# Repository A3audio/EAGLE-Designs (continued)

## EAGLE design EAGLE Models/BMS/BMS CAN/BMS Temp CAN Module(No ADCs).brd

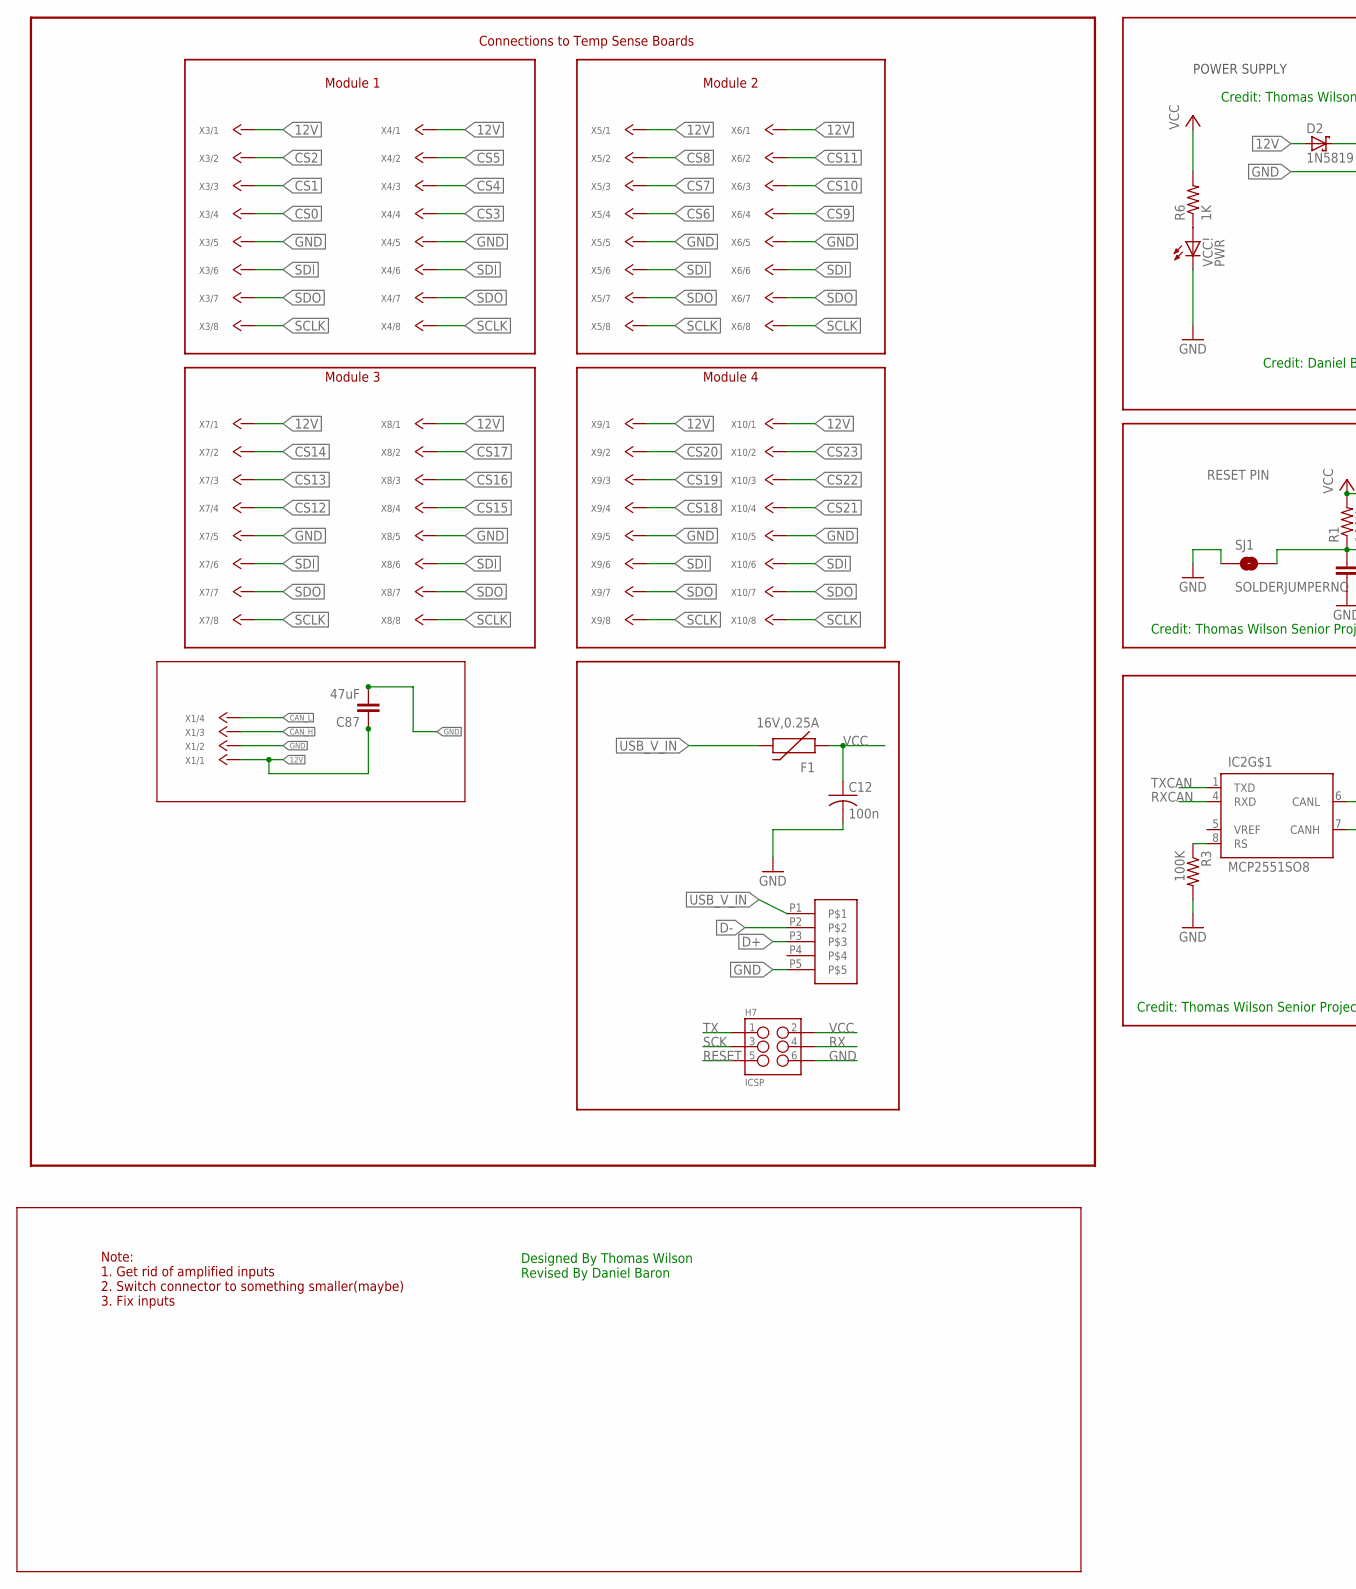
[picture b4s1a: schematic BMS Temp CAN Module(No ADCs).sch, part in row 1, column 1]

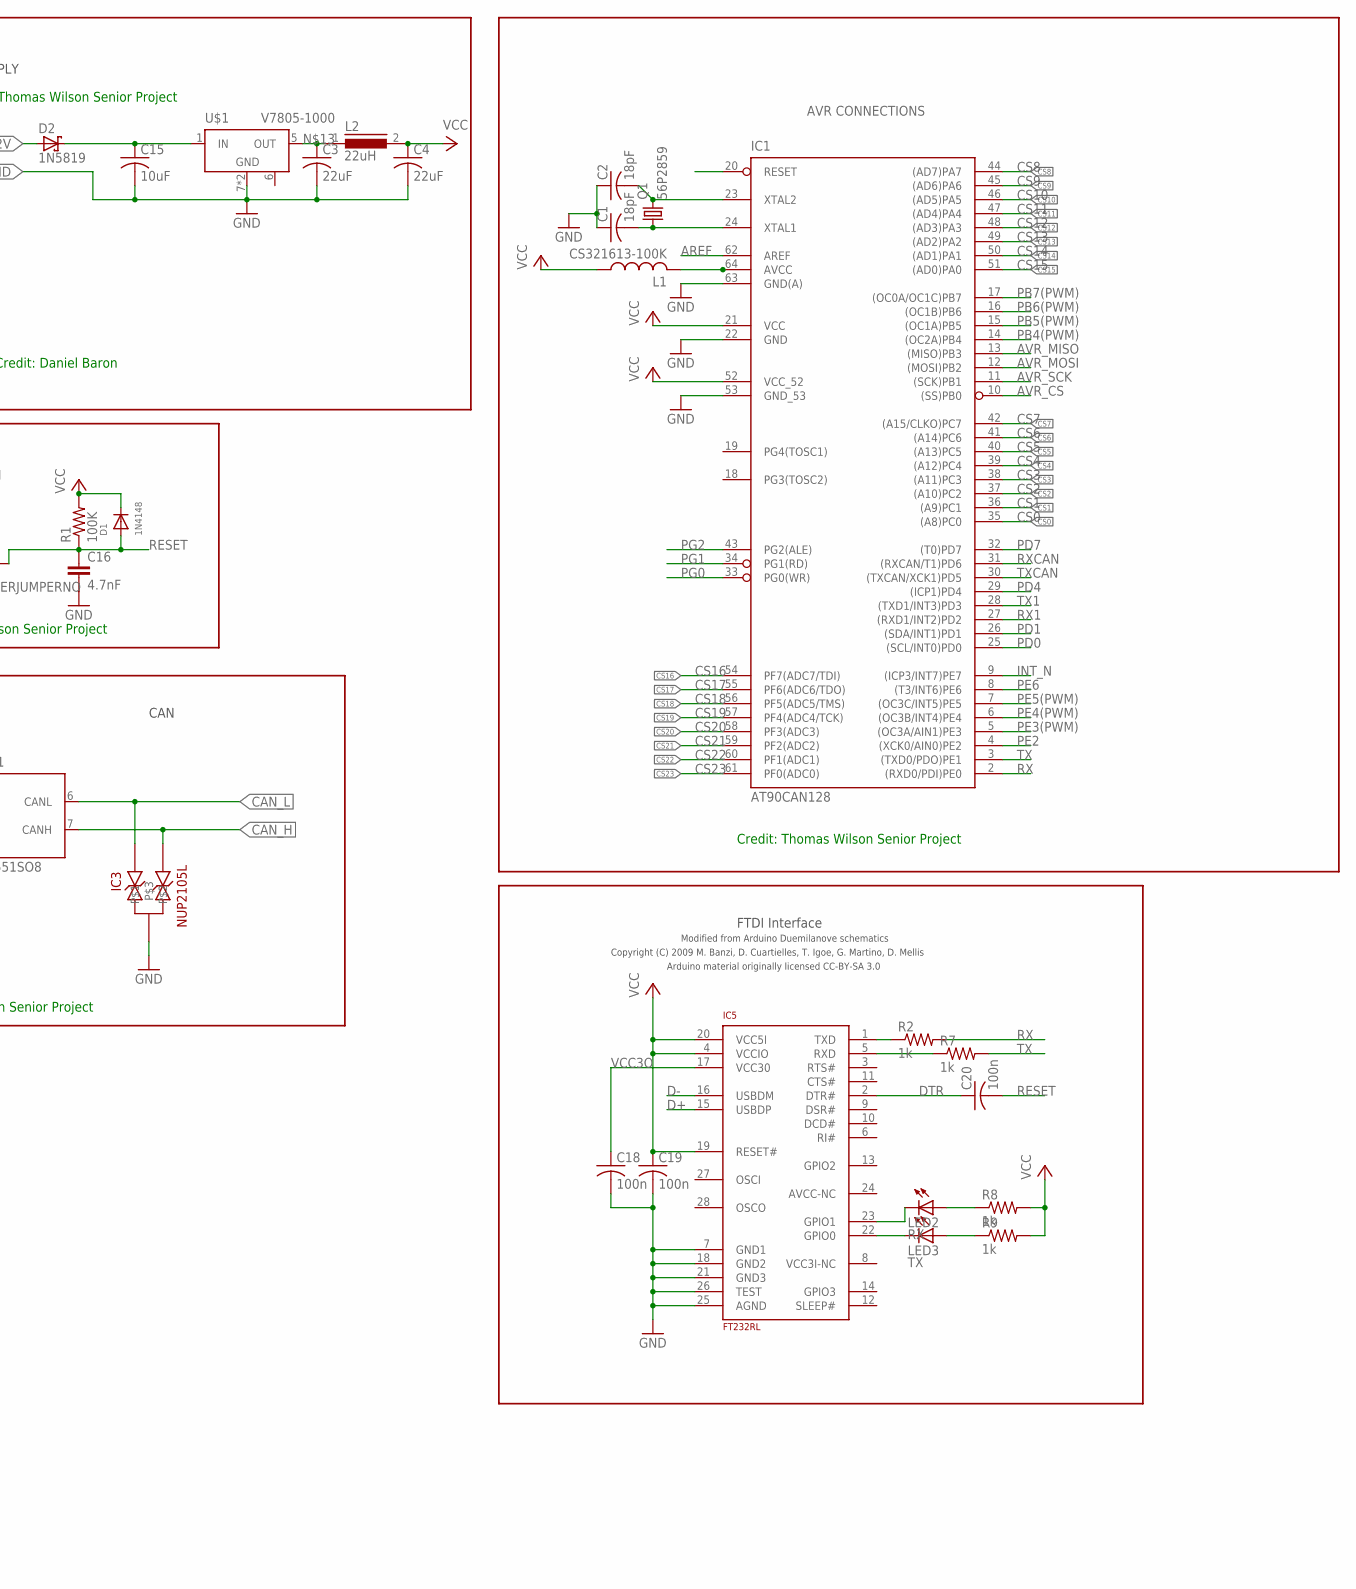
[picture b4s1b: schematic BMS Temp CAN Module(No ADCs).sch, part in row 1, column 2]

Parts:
C1, C2: 18pF; C0805
C3, C4: 22uF; C0805
C12, C18, C19, C20: 100n; C0805
C15: 10uF; C0805
C16: 4.7nF; 0603-CAP
C87: 47uF; C0805
D1: 1N4148; SOD-123
D2: 1N5819; DO41-7.6
F1: 16V,0.25A; PTC-1206
H7: ICSP; 2X3_SMD_FCI_54202-G30
IC1: AT90CAN128; TQFP64
IC2: MCP2551SO8; SO08
IC3: NUP2105L; SOT-23
IC5: FT232RL; SSOP28
L1: CS321613-100K; L3216C
L2: 22uH; DR73
LED2: RX; CHIPLED_0805
LED3: TX; CHIPLED_0805
Q1: 56P2859; HC49UP
R1, R3: 100K; R0805
R2, R7, R8, R9: 1k; R0805
R6: 1K; R0805
SJ1: SOLDERJUMPERNO; SJ_2S-NO
U$1: V7805-1000; V78XX-1000
U$14: MUSBB
VCC!: PWR; CHIPLED_0805
X1: 4_PIN_CONN; 4_PIN_MOLEX
X3, X4, X5, X6, X7, X8, X9, X10: 8_PIN_CONN; 8_PIN_MOLEX

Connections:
12V: C87.1, D2.A, X1.P$1, X3.P$1, X4.P$1, X5.P$1, X6.P$1, X7.P$1, X8.P$1, X9.P$1, X10.P$1
12V_PROTECTED: C15.1, D2.C, U$1.1 (IN)
AREF: IC1.62 (AREF)
AVR_CS: IC1.10 ((SS)PB0)
AVR_MISO: IC1.13 ((MISO)PB3)
AVR_MOSI: IC1.12 ((MOSI)PB2)
AVR_SCK: IC1.11 ((SCK)PB1)
CAN_H: IC2.7 (CANH), IC3.2, X1.P$3
CAN_L: IC2.6 (CANL), IC3.1, X1.P$4
CS0: IC1.35 ((A8)PC0), X3.P$4
CS1: IC1.36 ((A9)PC1), X3.P$3
CS2: IC1.37 ((A10)PC2), X3.P$2
CS3: IC1.38 ((A11)PC3), X4.P$4
CS4: IC1.39 ((A12)PC4), X4.P$3
CS5: IC1.40 ((A13)PC5), X4.P$2
CS6: IC1.41 ((A14)PC6), X5.P$4
CS7: IC1.42 ((A15/CLKO)PC7), X5.P$3
CS8: IC1.44 ((AD7)PA7), X5.P$2
CS9: IC1.45 ((AD6)PA6), X6.P$4
CS10: IC1.46 ((AD5)PA5), X6.P$3
CS11: IC1.47 ((AD4)PA4), X6.P$2
CS12: IC1.48 ((AD3)PA3), X7.P$4
CS13: IC1.49 ((AD2)PA2), X7.P$3
CS14: IC1.50 ((AD1)PA1), X7.P$2
CS15: IC1.51 ((AD0)PA0), X8.P$4
CS16: IC1.54 (PF7(ADC7/TDI)), X8.P$3
CS17: IC1.55 (PF6(ADC6/TDO)), X8.P$2
CS18: IC1.56 (PF5(ADC5/TMS)), X9.P$4
CS19: IC1.57 (PF4(ADC4/TCK)), X9.P$3
CS20: IC1.58 (PF3(ADC3)), X9.P$2
CS21: IC1.59 (PF2(ADC2)), X10.P$4
CS22: IC1.60 (PF1(ADC1)), X10.P$3
CS23: IC1.61 (PF0(ADC0)), X10.P$2
D+: IC5.15 (USBDP), U$14.P3
D-: IC5.16 (USBDM), U$14.P2
DTR: C20.1, IC5.2 (DTR#)
GND: C1.1, C2.1, C3.2, C4.2, C12.2, C15.2, C16.2, C18.2, C19.2, C87.2, H7.6, IC1.22 (GND), IC1.53 (GND_53), IC1.63 (GND(A)), IC2.2 (GND), IC3.3, IC5.7 (GND1), IC5.18 (GND2), IC5.21 (GND3), IC5.25 (AGND), IC5.26 (TEST), R3.2, SJ1.1, U$1.7 (GND), U$1.9 (GND), U$14.P5, VCC!.C, X1.P$2, X3.P$5, X4.P$5, X5.P$5, X6.P$5, X7.P$5, X8.P$5, X9.P$5, X10.P$5
GPIO0: IC5.22 (GPIO0), LED3.C
GPIO1: IC5.23 (GPIO1), LED2.C
INT_N: IC1.9 ((ICP3/INT7)PE7)
M8RXD: IC5.1 (TXD), R2.1
M8TXD: IC5.5 (RXD), R7.1
unnamed: IC2.8 (RS), R3.1
unnamed: R6.1, VCC!.A
unnamed: C1.2, IC1.24 (XTAL1), Q1.1
unnamed: C3.1, L2.1, U$1.5 (OUT)
unnamed: IC1.64 (AVCC), L1.2
unnamed: LED2.A, R8.1
unnamed: LED3.A, R9.1
PB4(PWM): IC1.14 ((OC2A)PB4)
PB5(PWM): IC1.15 ((OC1A)PB5)
PB6(PWM): IC1.16 ((OC1B)PB6)
PB7(PWM): IC1.17 ((OC0A/OC1C)PB7)
PD0: IC1.25 ((SCL/INT0)PD0)
PD1: IC1.26 ((SDA/INT1)PD1)
PD4: IC1.29 ((ICP1)PD4)
PD7: IC1.32 ((T0)PD7)
PE2: IC1.4 ((XCK0/AIN0)PE2)
PE3(PWM): IC1.5 ((OC3A/AIN1)PE3)
PE4(PWM): IC1.6 ((OC3B/INT4)PE4)
PE5(PWM): IC1.7 ((OC3C/INT5)PE5)
PE6: IC1.8 ((T3/INT6)PE6)
PG0: IC1.33 (PG0(WR))
PG1: IC1.34 (PG1(RD))
PG2: IC1.43 (PG2(ALE))
RESET: C16.1, C20.2, D1.A, H7.5, IC1.20 (RESET), R1.1, SJ1.2
RX: H7.4, IC1.2 ((RXD0/PDI)PE0), R2.2
RX1: IC1.27 ((RXD1/INT2)PD2)
RXCAN: IC1.31 ((RXCAN/T1)PD6), IC2.4 (RXD)
SCK: H7.3
SCLK: X3.P$8, X4.P$8, X5.P$8, X6.P$8, X7.P$8, X8.P$8, X9.P$8, X10.P$8
SDI: X3.P$6, X4.P$6, X5.P$6, X6.P$6, X7.P$6, X8.P$6, X9.P$6, X10.P$6
SDO: X3.P$7, X4.P$7, X5.P$7, X6.P$7, X7.P$7, X8.P$7, X9.P$7, X10.P$7
TX: H7.1, IC1.3 ((TXD0/PDO)PE1), R7.2
TX1: IC1.28 ((TXD1/INT3)PD3)
TXCAN: IC1.30 ((TXCAN/XCK1)PD5), IC2.1 (TXD)
USB_V_IN: F1.2, U$14.P1
VCC: C4.1, C12.1, C19.1, D1.C, F1.1, H7.2, IC1.21 (VCC), IC1.52 (VCC_52), IC2.3 (VCC), IC5.4 (VCCIO), IC5.19 (RESET#), IC5.20 (VCC5I), L1.1, L2.2, R1.2, R6.2, R8.2, R9.2
VCC3O: C18.1, IC5.17 (VCC30)
XTAL1: C2.2, IC1.23 (XTAL2), Q1.2

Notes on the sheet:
POWER SUPPLY
CAN
RESET PIN
AVR CONNECTIONS
FTDI Interface
Modified from Arduino Duemilanove schematics
Copyright (C) 2009 M. Banzi, D. Cuartielles, T. Igoe, G. Martino, D. Mellis
Arduino material originally licensed CC-BY-SA 3.0
Credit: Thomas Wilson Senior Project
Designed By Thomas Wilson Revised By Daniel Baron
Credit: Daniel Baron
Note: 1. Get rid of amplified inputs 2. Switch connector to something smaller(maybe) 3. Fix inputs
Connections to Temp Sense Boards
Module 1
Module 2
Module 3
Module 4

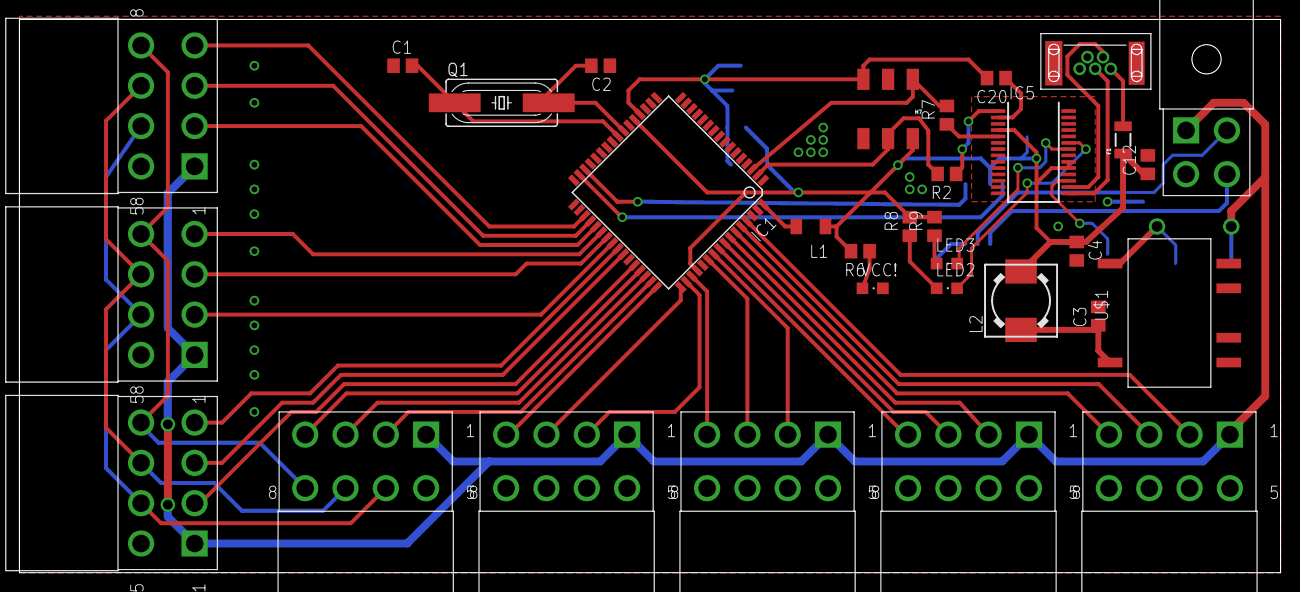
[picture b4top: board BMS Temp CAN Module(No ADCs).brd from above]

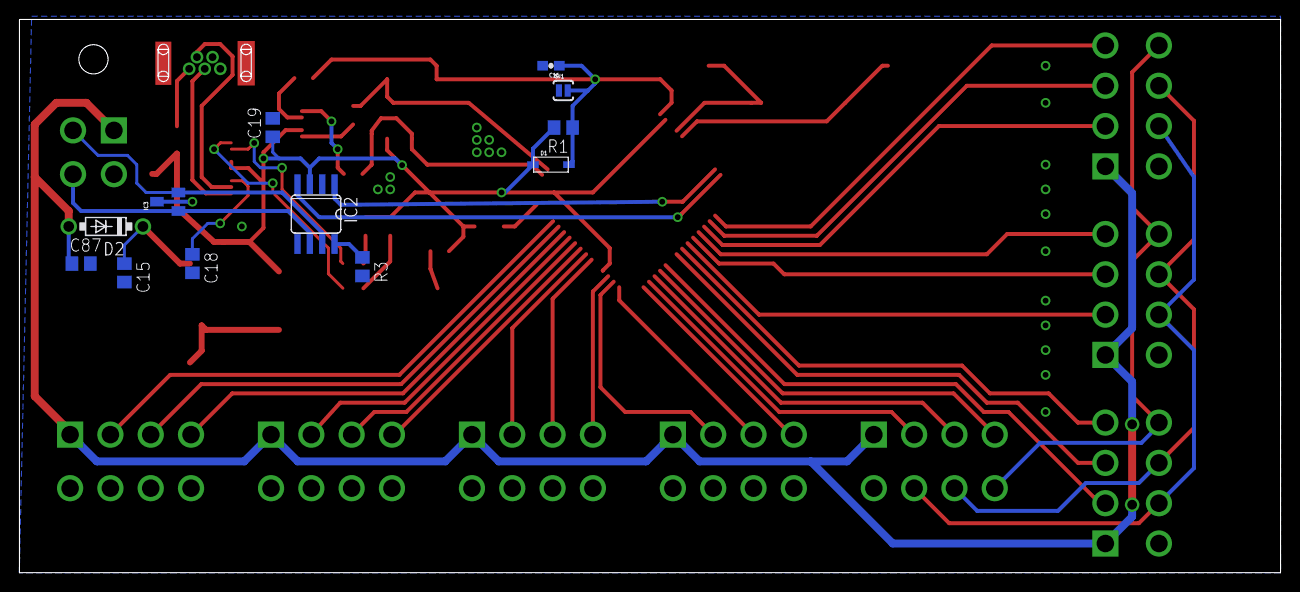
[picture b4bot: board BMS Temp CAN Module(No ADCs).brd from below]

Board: 2 copper layers, 129.5 x 56.8 mm, 44 parts (12 on the bottom side), 55 nets.

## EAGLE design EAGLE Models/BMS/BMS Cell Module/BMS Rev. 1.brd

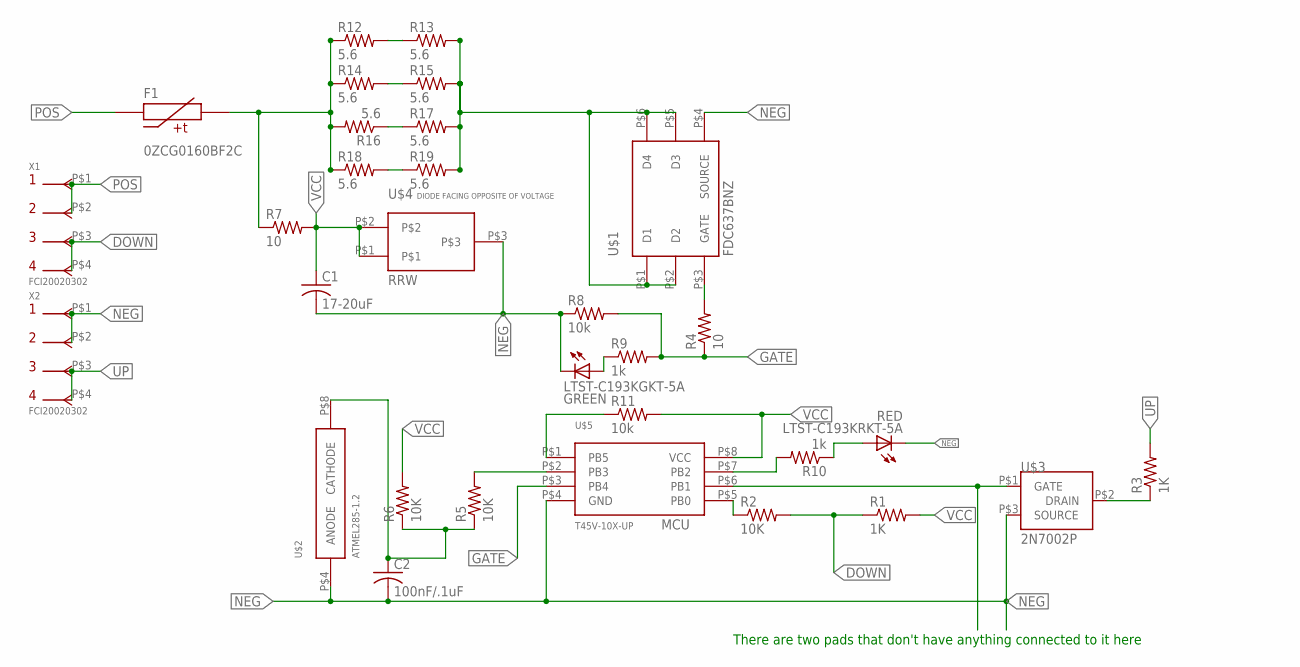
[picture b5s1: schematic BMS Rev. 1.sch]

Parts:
C1: 17-20uF; C0805
C2: 100nF/.1uF; C0805
F1: 0ZCG0160BF2C; 1812
LTST-C193KGKT-5A: GREEN; CHIPLED_1206
LTST-C193KRKT-5A: RED; CHIPLED_1206
R1, R3: 1K; R0805
R2, R5, R6: 10K; R0805
R4, R7: 10; R0805
R8, R11: 10k; R0805
R9, R10: 1k; R0805
R12, R13, R14, R15, R16, R17, R18, R19: 5.6; R1206
U$1: FDC637BNZ; SOT-23-6
U$2: ATMEL285-1.2; 8-SOIC
U$3: 2N7002P; SOT23-3
U$4: RRW; SOT23-3
U$5: T45V-10X-UP; TSSOP-8(ATMEL)
X1, X2: FCI20020302; 2_PIN_AMPHENOL

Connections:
DOWN: R1.1, R2.2, X1.P$3, X1.P$4
FUSE_OUT: F1.P$2, R7.1, R12.1, R14.1, R16.2, R18.1
GATE: R4.1, R8.2, R9.2, U$5.P$3 (PB4)
MOSFET_IN: R13.2, R15.2, R17.2, R19.2, U$1.P$1 (D1), U$1.P$2 (D2), U$1.P$5 (D3), U$1.P$6 (D4)
unnamed: C2.1, R5.1, R6.1, U$2.P$8 (CATHODE)
unnamed: R10.2, U$5.P$7 (PB2)
unnamed: R4.2, U$1.P$3 (GATE)
unnamed: R3.1, U$3.P$2 (DRAIN)
unnamed: R11.1, U$5.P$1 (PB5)
unnamed: R2.1, U$5.P$5 (PB0)
unnamed: R5.2, U$5.P$2 (PB3)
unnamed: LTST-C193KRKT-5A.A, R10.1
unnamed: R12.2, R13.1
unnamed: R16.1, R17.1
unnamed: LTST-C193KGKT-5A.A, R9.1
unnamed: R18.2, R19.1
unnamed: R14.2, R15.1
unnamed: U$3.P$1 (GATE), U$5.P$6 (PB1)
NEG: C1.2, C2.2, LTST-C193KGKT-5A.C, LTST-C193KRKT-5A.C, R8.1, U$1.P$4 (SOURCE), U$2.P$4 (ANODE), U$3.P$3 (SOURCE), U$4.P$3, U$5.P$4 (GND), X2.P$1, X2.P$2
POS: F1.P$1, X1.P$1, X1.P$2
UP: R3.2, X2.P$3, X2.P$4
VCC: C1.1, R1.2, R6.2, R7.2, R11.2, U$4.P$1, U$4.P$2, U$5.P$8 (VCC)

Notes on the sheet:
There are two pads that don't have anything connected to it here
MCU
DIODE FACING OPPOSITE OF VOLTAGE

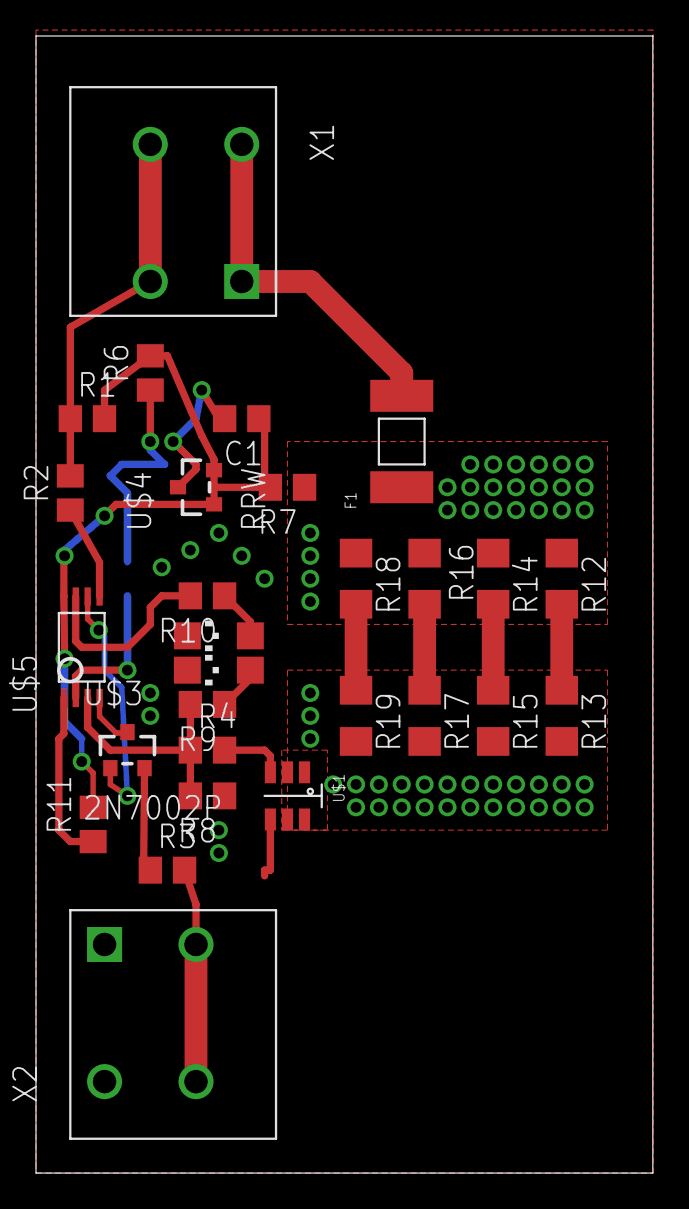
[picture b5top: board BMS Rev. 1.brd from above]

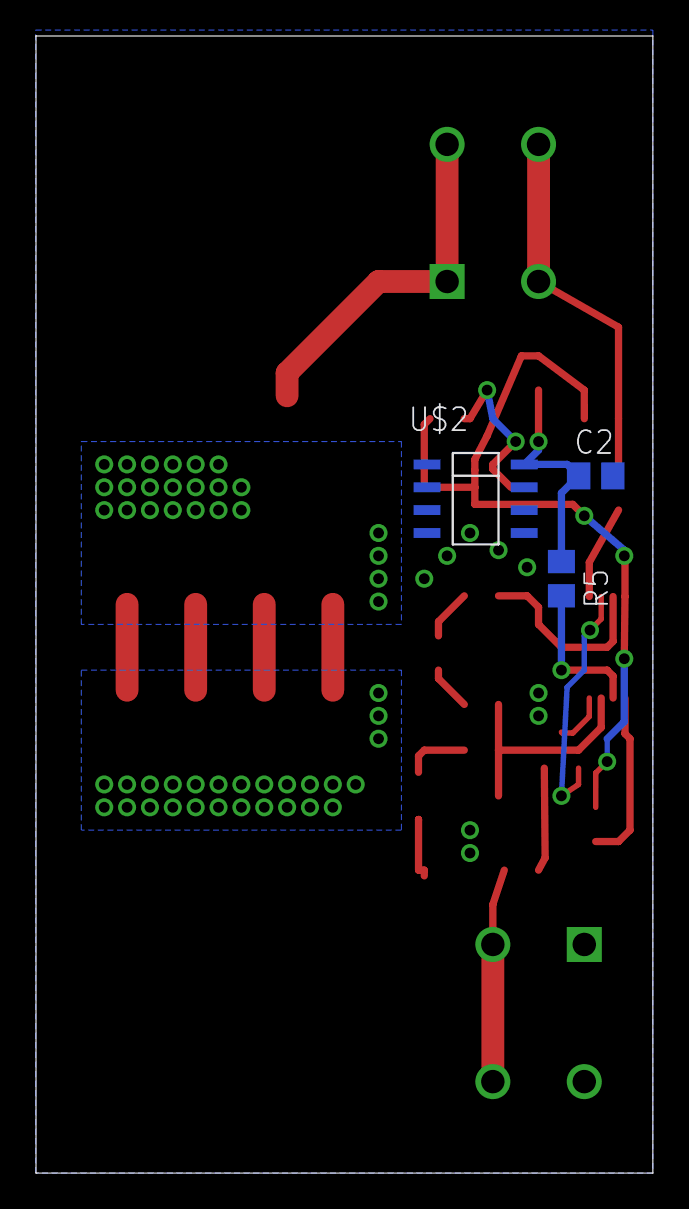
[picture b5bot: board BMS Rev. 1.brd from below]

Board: 2 copper layers, 34.3 x 63.2 mm, 31 parts (3 on the bottom side), 22 nets.
